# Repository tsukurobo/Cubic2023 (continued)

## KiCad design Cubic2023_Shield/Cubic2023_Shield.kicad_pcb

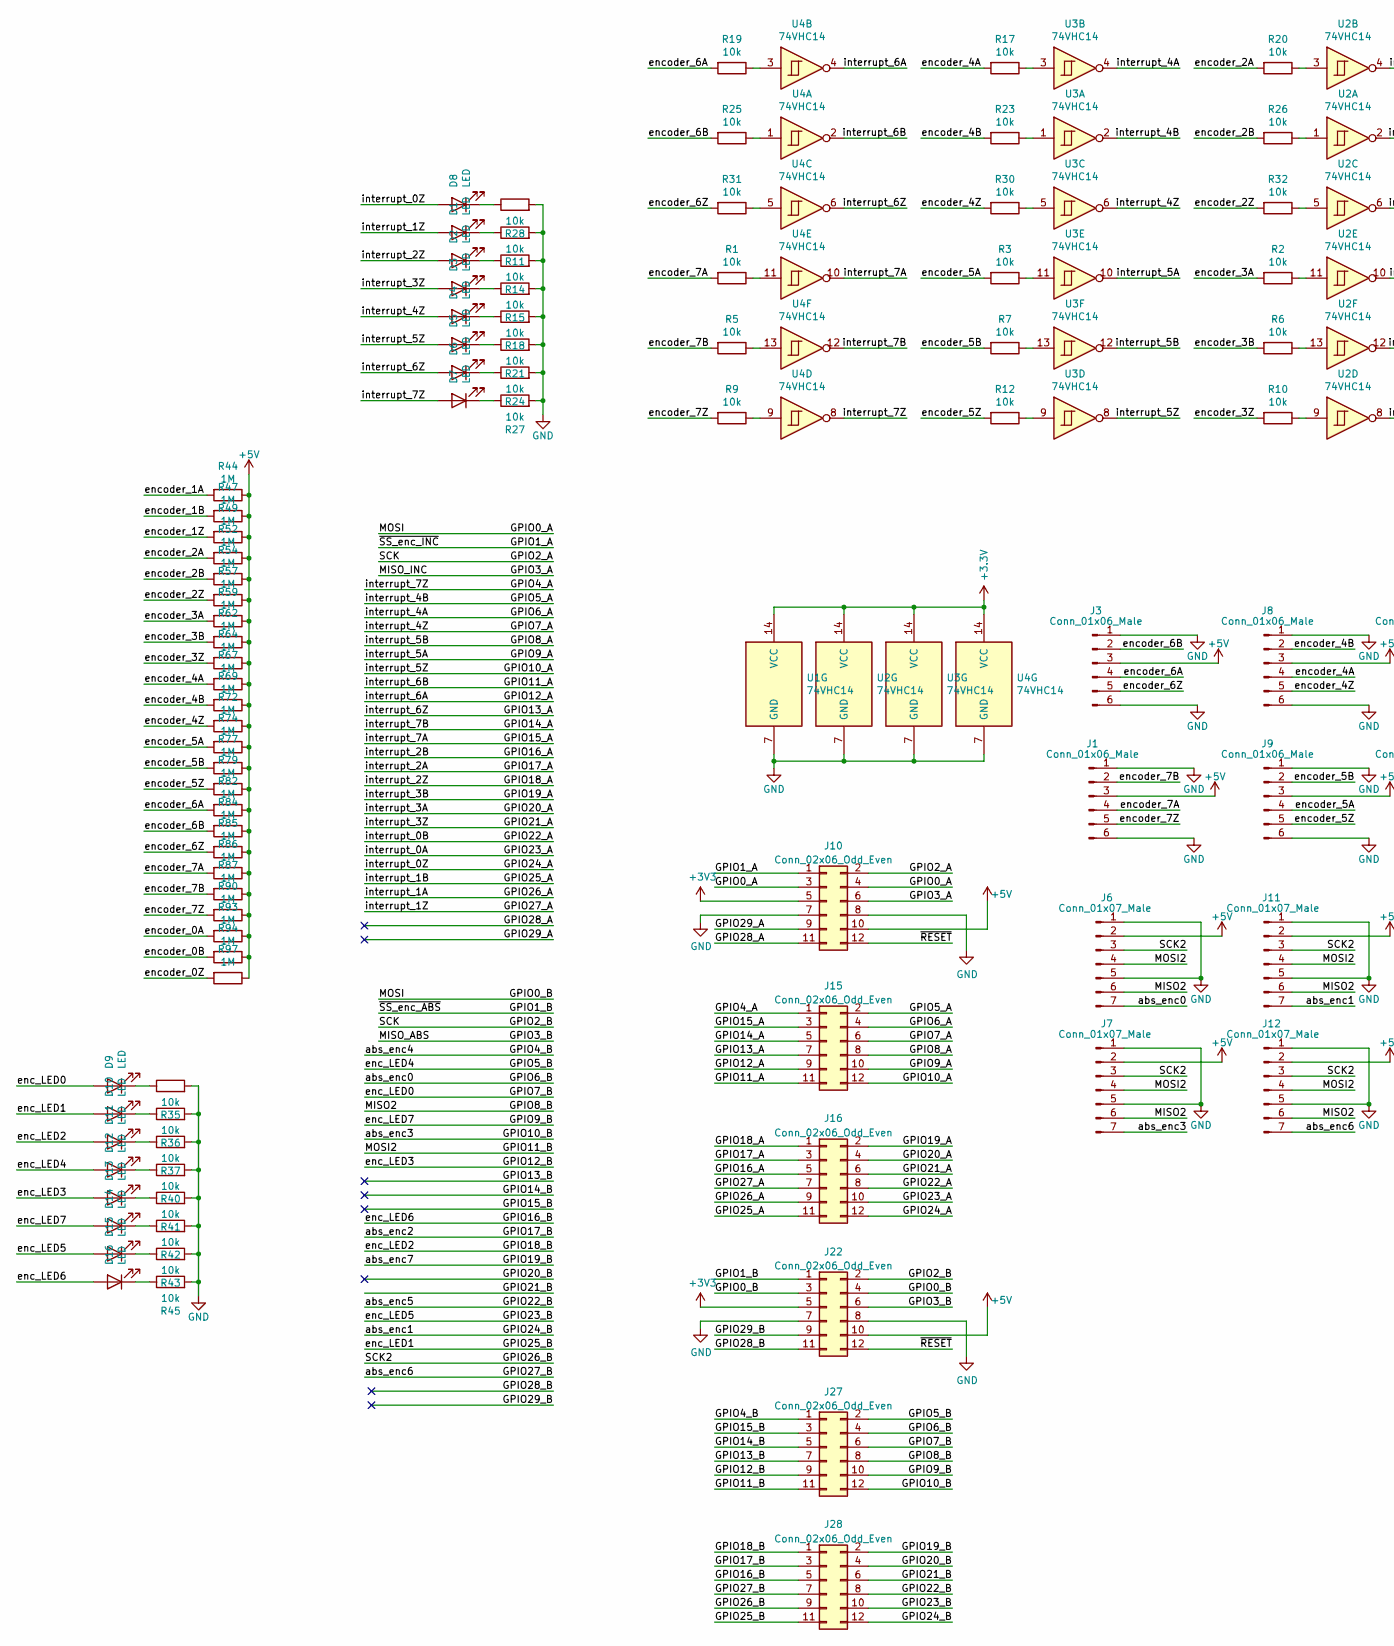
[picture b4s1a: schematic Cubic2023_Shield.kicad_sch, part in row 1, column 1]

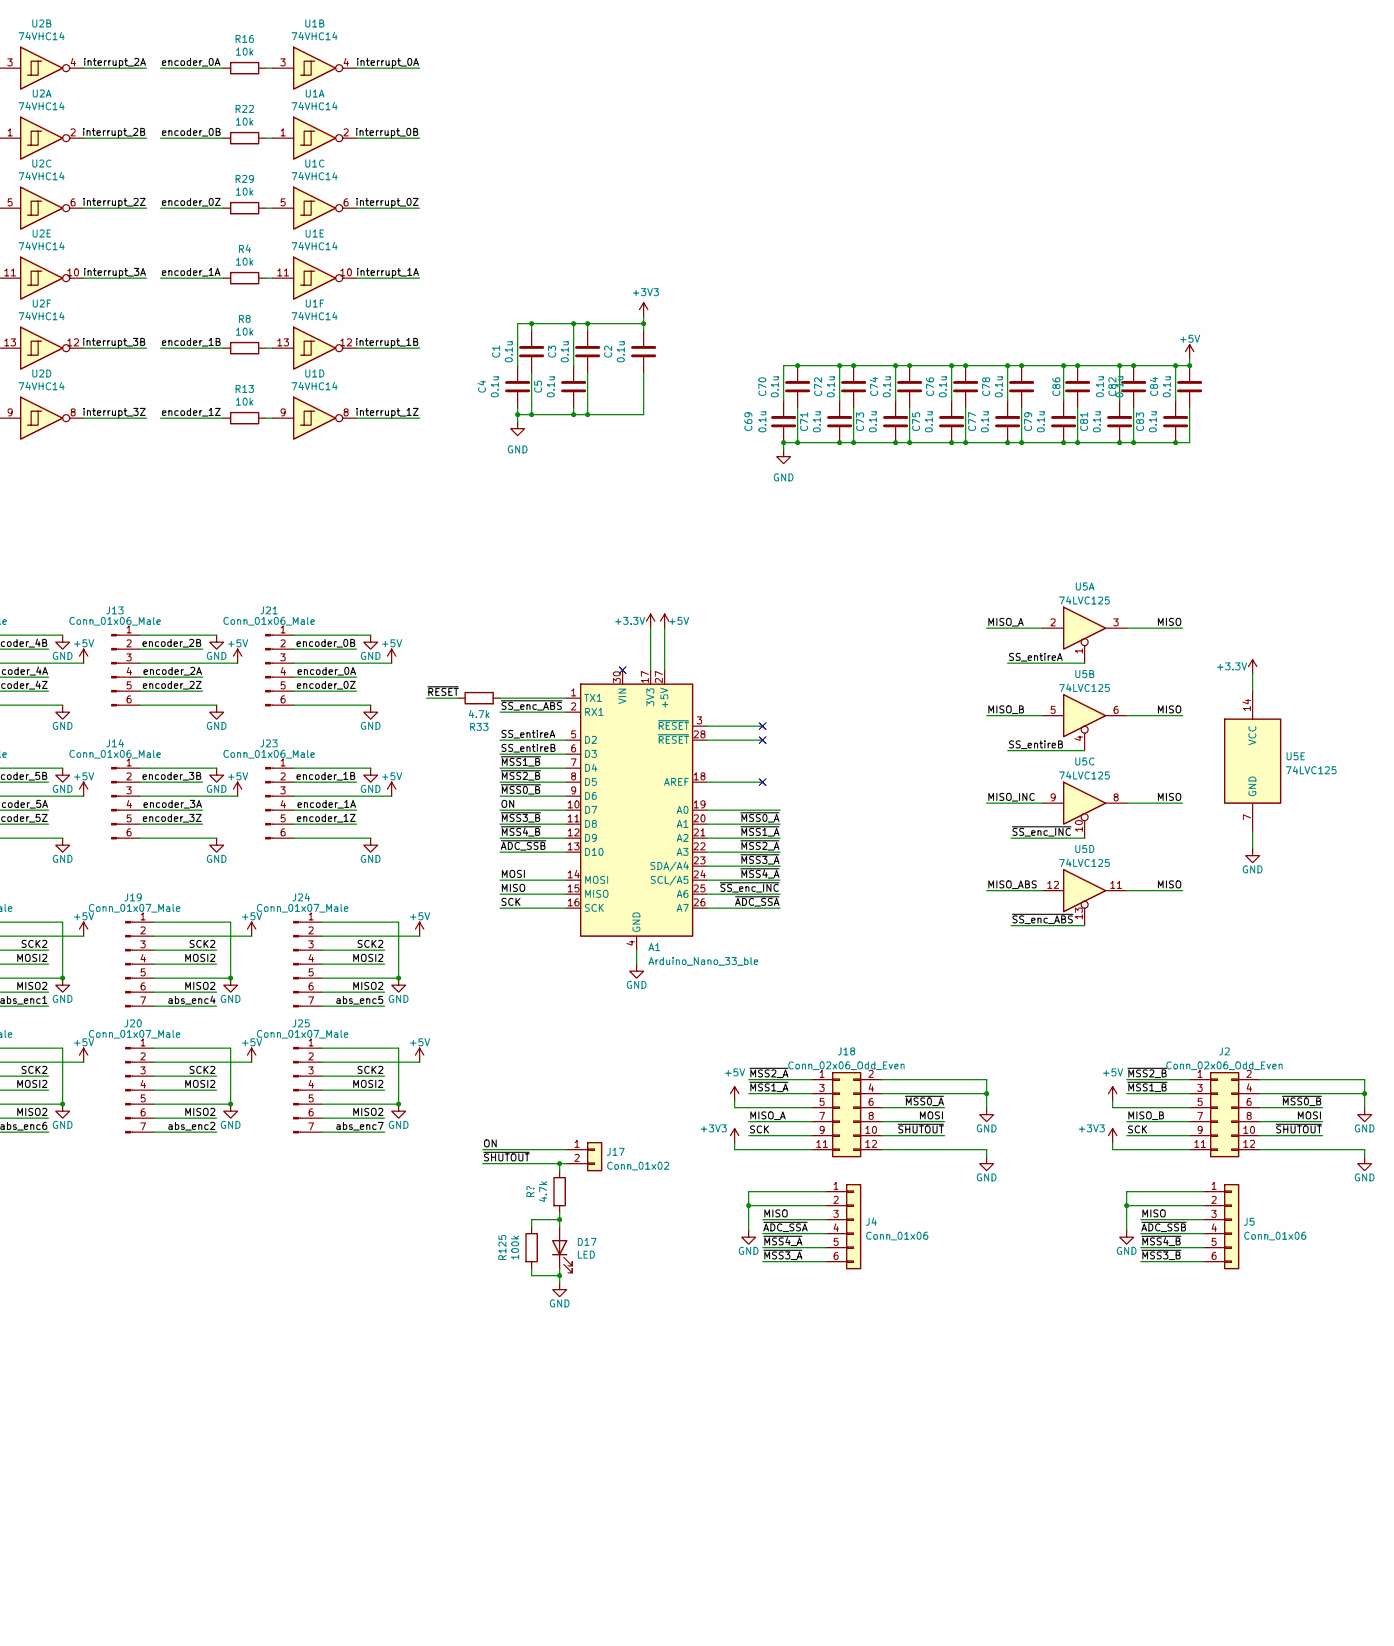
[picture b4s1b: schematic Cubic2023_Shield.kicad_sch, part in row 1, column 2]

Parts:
A1: Arduino_Nano_33_ble; Arduino_Nano
C1, C2, C3, C4, C5, C69, C70, C71, C72, C73, C74, C75, C76, C77, C78, C79, C81, C82, C83, C84, C86: 0.1u; C_0402_1005Metric_Pad0.74x0.62mm_HandSolder; LCSC C307331
D1, D2, D3, D4, D5, D6, D7, D8, D9, D10, D11, D12, D13, D14, D15, D16, D17: LED; LED_0603_1608Metric_Pad1.05x0.95mm_HandSolder; LCSC C72041
J1, J3, J8, J9, J13, J14, J21, J23: Conn_01x06_Male; PinSocket_1x06_P2.00mm_Vertical
J2, J18: Conn_02x06_Odd_Even; PinSocket_2x06_P2.54mm_Horizontal
J4, J5: Conn_01x06; PinSocket_1x06_P2.54mm_Horizontal
J6, J7, J11, J12, J19, J20, J24, J25: Conn_01x07_Male; PinSocket_1x07_P2.00mm_Vertical
J10, J15, J16, J22, J27, J28: Conn_02x06_Odd_Even; PinHeader_2x06_P1.27mm_Vertical
J17: Conn_01x02; PinSocket_1x02_P2.54mm_Vertical
R1, R2, R3, R4, R5, R6, R7, R8, R9, R10, R11, R12, R13, R14, R15, R16, R17, R18, R19, R20, R21, R22, R23, R24, R25, R26, R27, R28, R29, R30, R31, R32, R35, R36, R37, R40, R41, R42, R43, R45: 10k; R_0603_1608Metric; LCSC C25804
R33: 4.7k; R_0603_1608Metric
R44, R47, R49, R52, R54, R57, R59, R62, R64, R67, R69, R72, R74, R77, R79, R82, R84, R85, R86, R87, R90, R93, R94, R97: 1M; R_0603_1608Metric; LCSC C22935
R125: 100k; R_0603_1608Metric; LCSC C25803
U1, U2, U3, U4: 74VHC14; TSSOP-14_4.4x5mm_P0.65mm; LCSC C6145
U5: 74LVC125; SO-14_3.9x8.65mm_P1.27mm; LCSC C460512

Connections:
+5V: A1.27 (+5V), C69.2, C70.2, C71.2, C72.2, C73.2, C74.2, C75.2, C76.2, C77.2, C78.2, C79.2, C81.2, C82.2, C83.2, C84.2, C86.2, J1.3, J2.5, J3.3, J6.2, J7.2, J8.3, J9.3, J10.10, J11.2, J12.2, J13.3, J14.3, J18.5, J19.2, J20.2, J21.3, J22.10, J23.3, J24.2, J25.2, R44.1, R47.1, R49.1, R52.1, R54.1, R57.1, R59.1, R62.1, R64.1, R67.1, R69.1, R72.1, R74.1, R77.1, R79.1, R82.1, R84.1, R85.1, R86.1, R87.1, R90.1, R93.1, R94.1, R97.1
/GPIO0_A: A1.14 (MOSI), J2.8, J10.3, J10.4, J18.8, J22.3, J22.4
/GPIO1_A: A1.25 (A6), J10.1, U5.10
/GPIO1_B: A1.2 (RX1), J22.1, U5.13
/GPIO2_A: A1.16 (SCK), J2.9, J10.2, J18.9, J22.2
/GPIO3_A: J10.6, U5.9
/GPIO3_B: J22.6, U5.12
/GPIO4_A: D7.2 (A), J15.1, U4.8
/GPIO4_B: J19.7, J27.1
/GPIO5_A: J15.2, U3.2
/GPIO5_B: D12.2 (A), J27.2
/GPIO6_A: J15.4, U3.4
/GPIO6_B: J6.7, J27.4
/GPIO7_A: D4.2 (A), J15.6, U3.6
/GPIO7_B: D9.2 (A), J27.6
/GPIO8_A: J15.8, U3.12
/GPIO8_B: J6.6, J7.6, J11.6, J12.6, J19.6, J20.6, J24.6, J25.6, J27.8
/GPIO9_A: J15.10, U3.10
/GPIO9_B: D14.2 (A), J27.10
/GPIO10_A: D5.2 (A), J15.12, U3.8
/GPIO10_B: J7.7, J27.12
/GPIO11_A: J15.11, U4.2
/GPIO11_B: J6.4, J7.4, J11.4, J12.4, J19.4, J20.4, J24.4, J25.4, J27.11
/GPIO12_A: J15.9, U4.4
/GPIO12_B: D13.2 (A), J27.9
/GPIO13_A: D6.2 (A), J15.7, U4.6
/GPIO13_B: J27.7
/GPIO14_A: J15.5, U4.12
/GPIO14_B: J27.5
/GPIO15_A: J15.3, U4.10
/GPIO15_B: J27.3
/GPIO16_A: J16.5, U2.2
/GPIO16_B: D16.2 (A), J28.5
/GPIO17_A: J16.3, U2.4
/GPIO17_B: J20.7, J28.3
/GPIO18_A: D2.2 (A), J16.1, U2.6
/GPIO18_B: D11.2 (A), J28.1
/GPIO19_A: J16.2, U2.12
/GPIO19_B: J25.7, J28.2
/GPIO20_A: J16.4, U2.10
/GPIO20_B: J28.4
/GPIO21_A: D3.2 (A), J16.6, U2.8
/GPIO21_B: J28.6
/GPIO22_A: J16.8, U1.2
/GPIO22_B: J24.7, J28.8
/GPIO23_A: J16.10, U1.4
/GPIO23_B: D15.2 (A), J28.10
/GPIO24_A: D8.2 (A), J16.12, U1.6
/GPIO24_B: J11.7, J28.12
/GPIO25_A: J16.11, U1.12
/GPIO25_B: D10.2 (A), J28.11
/GPIO26_A: J16.9, U1.10
/GPIO26_B: J6.3, J7.3, J11.3, J12.3, J19.3, J20.3, J24.3, J25.3, J28.9
/GPIO27_A: D1.2 (A), J16.7, U1.8
/GPIO27_B: J12.7, J28.7
/GPIO28_A: J10.11
/GPIO28_B: J22.11
/GPIO29_A: J10.9
/GPIO29_B: J22.9
/MISO: A1.15 (MISO), J4.3, J5.3, U5.3, U5.6, U5.8, U5.11
/MISO_A: J18.7, U5.2
/MISO_B: J2.7, U5.5
/ON: A1.10 (D7), J17.1
/SS_entireA: A1.5 (D2), U5.1
/SS_entireB: A1.6 (D3), U5.4
/encoder_0A: J21.4, R16.2, R93.2
/encoder_0B: J21.2, R22.2, R94.2
/encoder_0Z: J21.5, R29.2, R97.2
/encoder_1A: J23.4, R4.2, R44.2
/encoder_1B: J23.2, R8.2, R47.2
/encoder_1Z: J23.5, R13.2, R49.2
/encoder_2A: J13.4, R20.2, R52.2
/encoder_2B: J13.2, R26.2, R54.2
/encoder_2Z: J13.5, R32.2, R57.2
/encoder_3A: J14.4, R2.2, R59.2
/encoder_3B: J14.2, R6.2, R62.2
/encoder_3Z: J14.5, R10.2, R64.2
/encoder_4A: J8.4, R17.2, R67.2
/encoder_4B: J8.2, R23.2, R69.2
/encoder_4Z: J8.5, R30.2, R72.2
/encoder_5A: J9.4, R3.2, R74.2
/encoder_5B: J9.2, R7.2, R77.2
/encoder_5Z: J9.5, R12.2, R79.2
/encoder_6A: J3.4, R19.2, R82.2
/encoder_6B: J3.2, R25.2, R84.2
/encoder_6Z: J3.5, R31.2, R85.2
/encoder_7A: J1.4, R1.2, R86.2
/encoder_7B: J1.2, R5.2, R87.2
/encoder_7Z: J1.5, R9.2, R90.2
/~ADC_SSA: A1.26 (A7), J4.4
/~ADC_SSB: A1.13 (D10), J5.4
/~MSS0_A: A1.20 (A1), J18.6
/~MSS0_B: A1.9 (D6), J2.6
/~MSS1_A: A1.21 (A2), J18.3
/~MSS1_B: A1.7 (D4), J2.3
/~MSS2_A: A1.22 (A3), J18.1
/~MSS2_B: A1.8 (D5), J2.1
/~MSS3_A: A1.23 (SDA/A4), J4.6
/~MSS3_B: A1.11 (D8), J5.6
/~MSS4_A: A1.24 (SCL/A5), J4.5
/~MSS4_B: A1.12 (D9), J5.5
/~RESET: J10.12, J22.12, R33.1
/~SHUTOUT: J2.10, J17.2, J18.10; also elsewhere on the board
GND: A1.4 (GND), A1.29 (GND), C1.1, C2.1, C3.1, C4.1, C5.1, C69.1, C70.1, C71.1, C72.1, C73.1, C74.1, C75.1, C76.1, C77.1, C78.1, C79.1, C81.1, C82.1, C83.1, C84.1, C86.1, D17.1 (K), J1.1, J1.6, J2.2, J2.4, J2.12, J3.1, J3.6, J4.1, J4.2, J5.1, J5.2, J6.1, J6.5, J7.1, J7.5, J8.1, J8.6, J9.1, J9.6, J10.7, J10.8, J11.1, J11.5, J12.1, J12.5, J13.1, J13.6, J14.1, J14.6, J18.2, J18.4, J18.12, J19.1, J19.5, J20.1, J20.5, J21.1, J21.6, J22.7, J22.8, J23.1, J23.6, J24.1, J24.5, J25.1, J25.5, R11.2, R14.2, R15.2, R18.2, R21.2, R24.2, R27.2, R28.2, R35.2, R36.2, R37.2, R40.2, R41.2, R42.2, R43.2, R45.2, R125.2, U1.7 (GND), U2.7 (GND), U3.7 (GND), U4.7 (GND), U5.7 (GND)
unnamed: A1.1 (TX1), R33.2
unnamed: D1.1 (K), R11.1
unnamed: D2.1 (K), R14.1
unnamed: D3.1 (K), R15.1
unnamed: D4.1 (K), R18.1
unnamed: D5.1 (K), R21.1
unnamed: D6.1 (K), R24.1
unnamed: D7.1 (K), R27.1
unnamed: D8.1 (K), R28.1
unnamed: D9.1 (K), R35.1
unnamed: D10.1 (K), R36.1
unnamed: D11.1 (K), R37.1
unnamed: D12.1 (K), R40.1
unnamed: D13.1 (K), R41.1
unnamed: D14.1 (K), R42.1
unnamed: D15.1 (K), R43.1
unnamed: D16.1 (K), R45.1
unnamed 121: D17.2 (A), R125.1; also elsewhere on the board
unnamed: R1.1, U4.11
unnamed: R2.1, U2.11
unnamed: R3.1, U3.11
unnamed: R4.1, U1.11
unnamed: R5.1, U4.13
unnamed: R6.1, U2.13
unnamed: R7.1, U3.13
unnamed: R8.1, U1.13
unnamed: R9.1, U4.9
unnamed: R10.1, U2.9
unnamed: R12.1, U3.9
unnamed: R13.1, U1.9
unnamed: R16.1, U1.3
unnamed: R17.1, U3.3
unnamed: R19.1, U4.3
unnamed: R20.1, U2.3
unnamed: R22.1, U1.1
unnamed: R23.1, U3.1
unnamed: R25.1, U4.1
unnamed: R26.1, U2.1
unnamed: R29.1, U1.5
unnamed: R30.1, U3.5
unnamed: R31.1, U4.5
unnamed: R32.1, U2.5

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
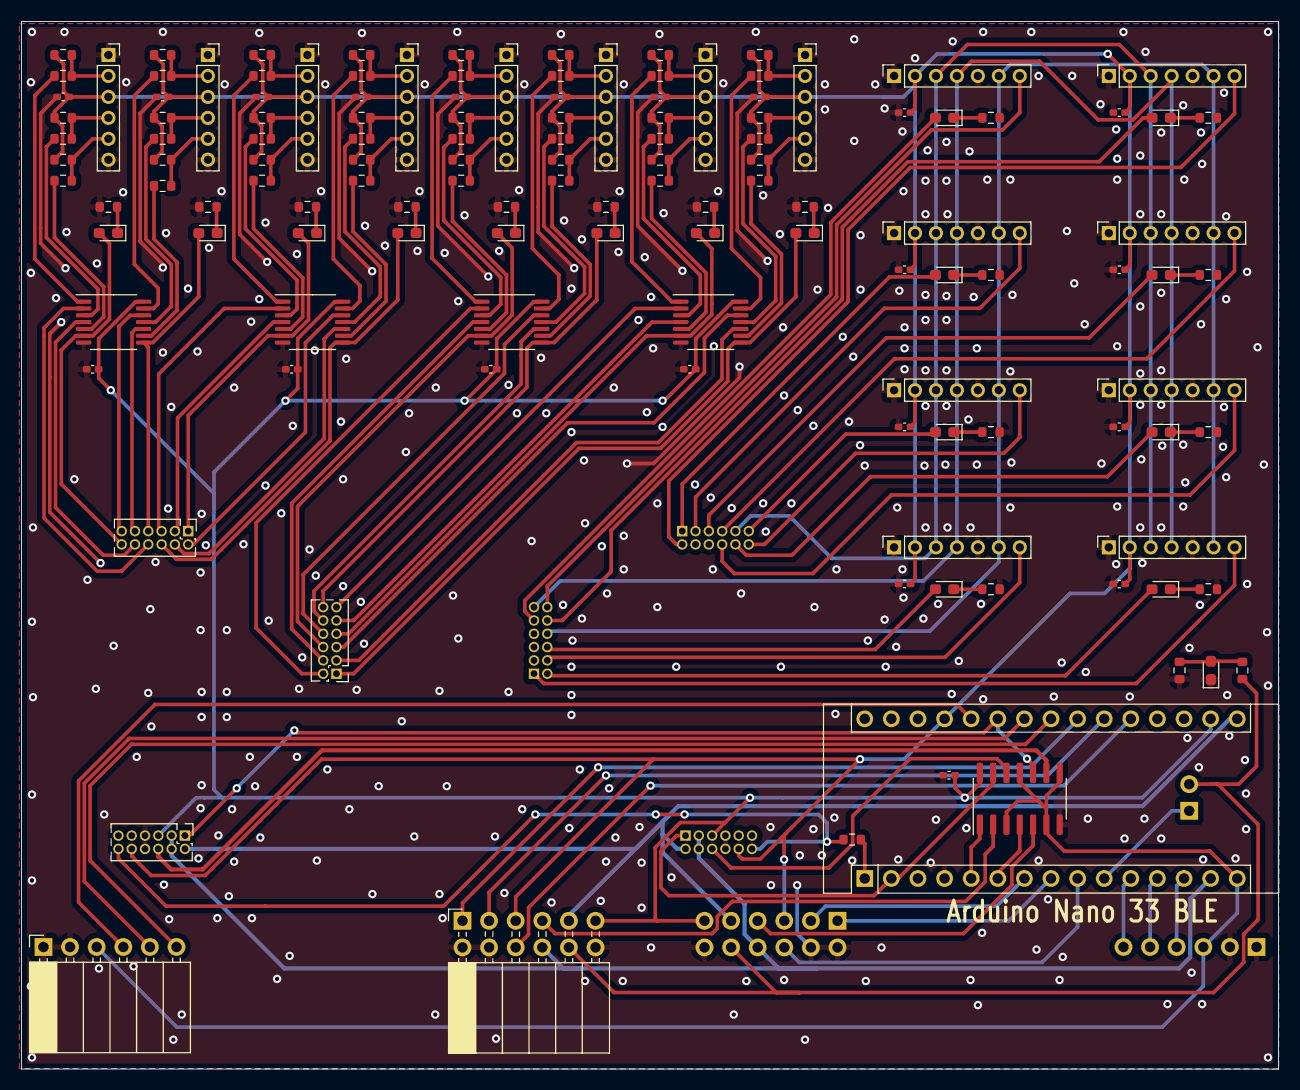
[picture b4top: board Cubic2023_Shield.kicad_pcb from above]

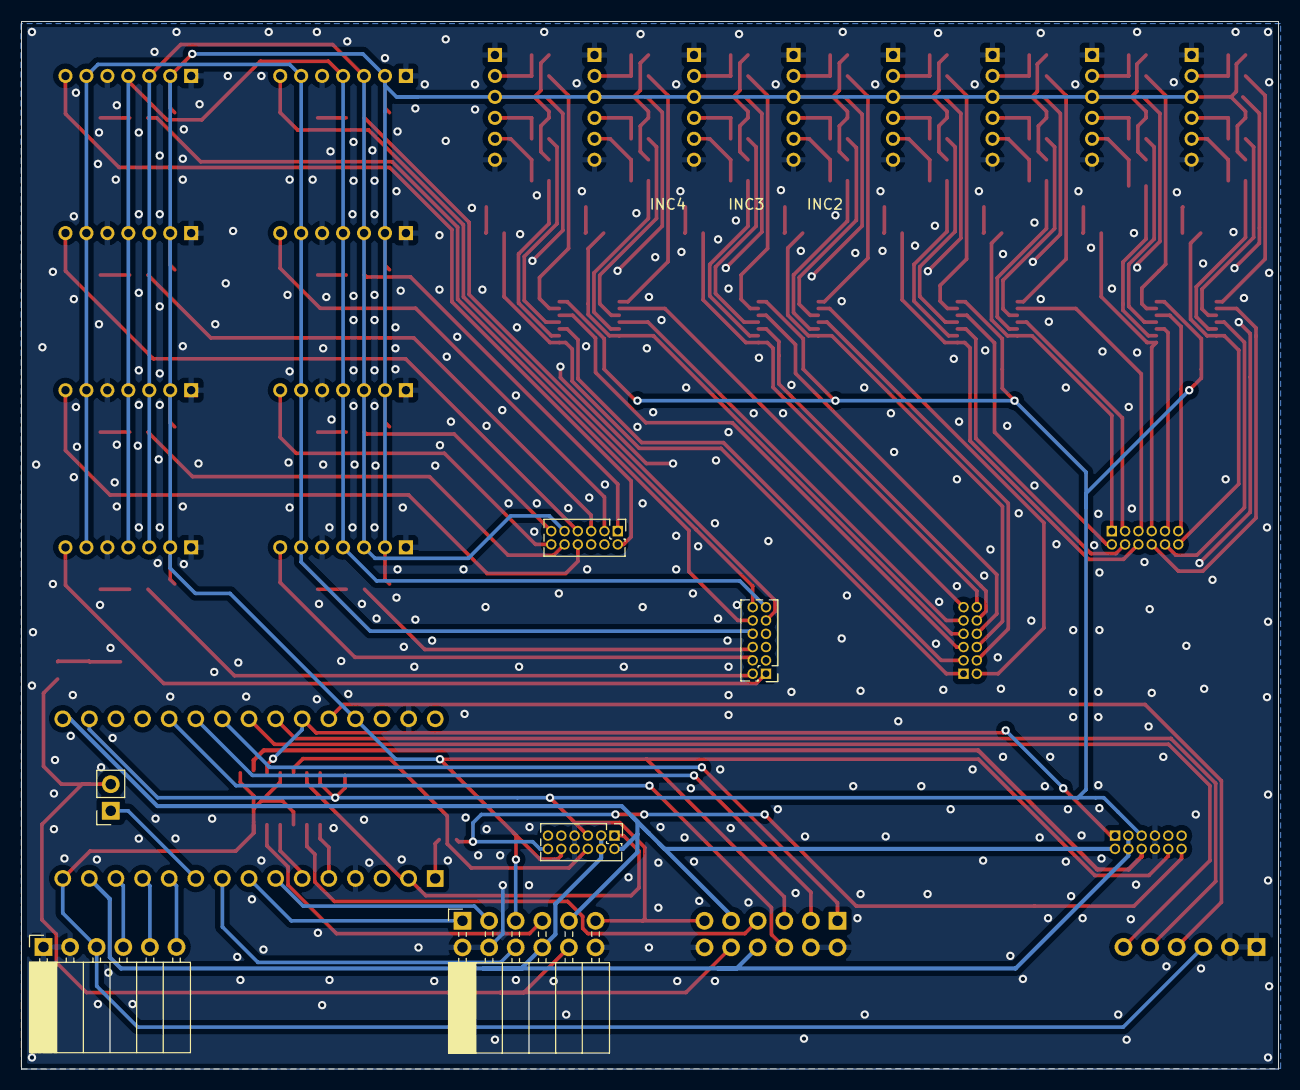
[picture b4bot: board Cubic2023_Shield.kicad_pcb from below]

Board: 2 copper layers, 120.0 x 100.0 mm, 138 parts (6 on the bottom side), 138 nets.

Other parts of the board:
R34: 4.7k; R_0603_1608Metric

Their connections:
/~SHUTOUT: R34.1; also elsewhere on the board
unnamed 121: R34.2; also elsewhere on the board

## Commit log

2023-07-28 Before revision
